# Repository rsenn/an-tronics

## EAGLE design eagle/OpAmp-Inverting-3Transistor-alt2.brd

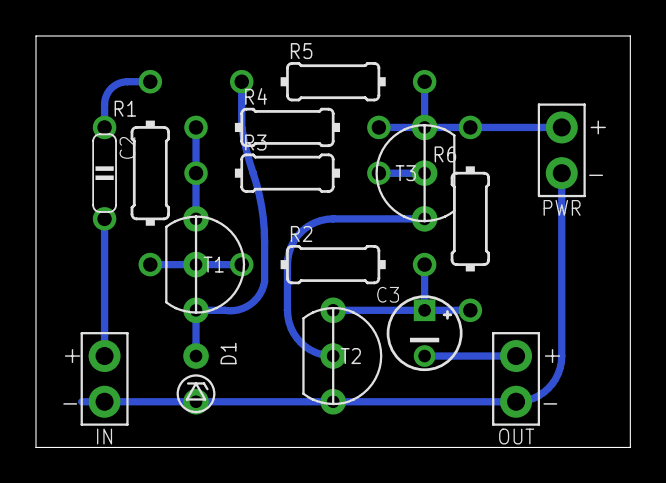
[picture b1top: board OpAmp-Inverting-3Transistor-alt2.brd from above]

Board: 2 copper layers, 33.0 x 22.9 mm, 15 parts (0 on the bottom side), 11 nets.

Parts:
C2: 33nF; C050-020X044
C3: 3.3μF; E2.5-4/V
D1: Z=3.3V; DO34Z2,5
IN: SPAD+--+; SPAD-+
J1: PWR-R
OUT: SPAD+-+-; SPAD+-
R1: 100kΩ; 0204/10-V
R2: 1MΩ; 0204/10
R3: 75kΩ; 0204/10
R4: 7.5kΩ; 0204/10
R5: 4.7kΩ; 0204/10
R6: 1kΩ; 0204/10-V
T1, T2: BC547; TO92-CBE
T3: BC557; TO92-CBE

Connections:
GND: D1.A, IN.1, J1.1, OUT.1, T2.E
unnamed: D1.C, R5.1, T1.E
unnamed: R3.1, R4.1, T1.C
unnamed: T2.B, T3.C
unnamed: C2.2, IN.2
unnamed: C2.1, R1.1
unnamed: R1.2, R2.1, T1.B
unnamed: R3.2, T3.B
unnamed: C3.+, R2.2, R6.2, T2.C
unnamed: C3.-, OUT.2
VCC: J1.2, R4.2, R5.2, R6.1, T3.E

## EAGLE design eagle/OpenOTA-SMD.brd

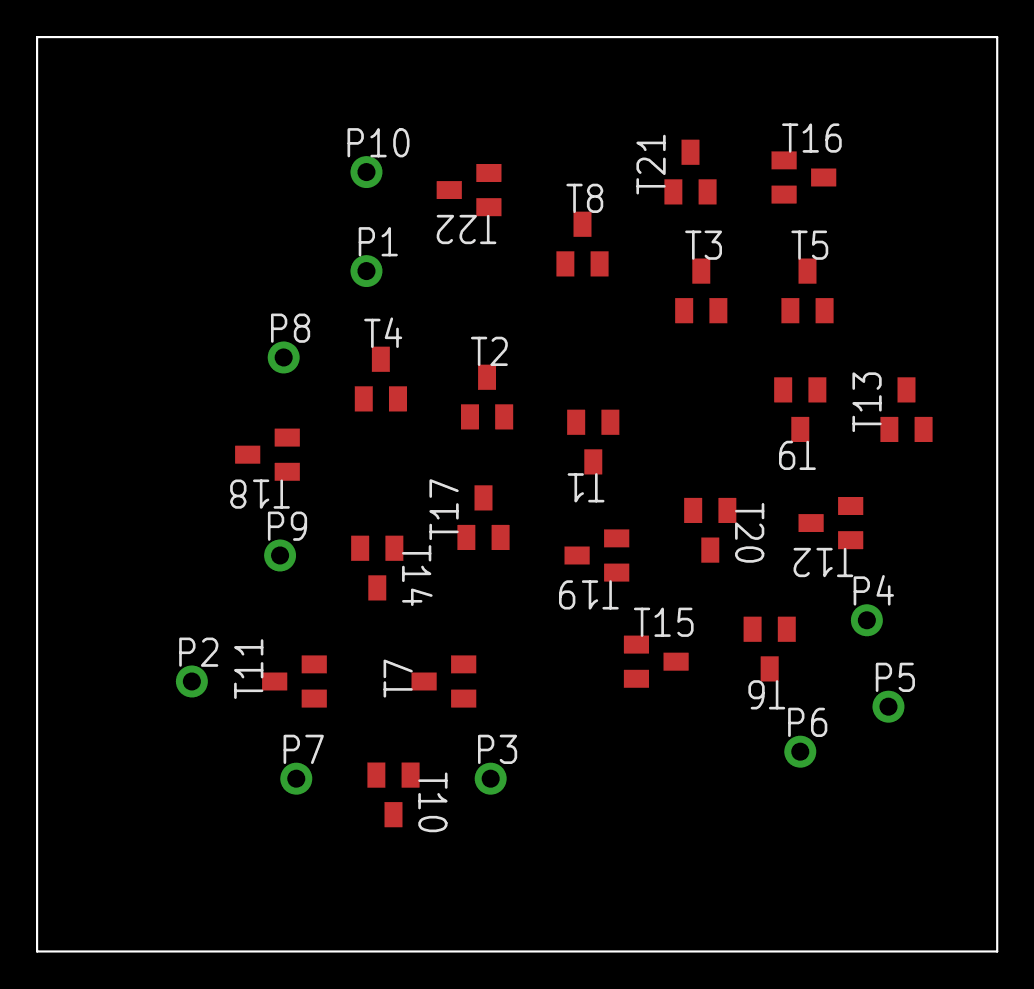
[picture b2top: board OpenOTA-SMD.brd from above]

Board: 2 copper layers, 53.3 x 50.8 mm, 32 parts (0 on the bottom side), 22 nets, no tracks yet.

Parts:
P1, P2, P3, P4, P5, P6, P7, P8, P9, P10: SPAD
T1, T2, T3, T4, T5, T6, T7, T8, T9: BC857; SOT-23
T10, T12, T13, T14, T15, T16, T17, T18, T19, T20, T21, T22: BC847; SOT-23_T10
T11: BC847; SOT-23

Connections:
+15: P1.1, T1.2, T2.2, T3.2, T4.2, T5.2, T6.2
-15: P10.1, T17.2, T18.2, T19.2, T20.2, T21.2, T22.2
IN_A+: P3.1, T10.1
IN_A-: P7.1, T11.1
IN_B+: P5.1, T13.1
IN_B-: P4.1, T12.1
IO_A: P2.1, T7.3, T11.3
I_A: P8.1, T14.1, T17.3
I_B: P9.1, T15.1, T19.3
unnamed: T1.1, T2.1, T2.3, T7.2
unnamed: T1.3, T7.1, T10.3
unnamed: T12.2, T13.2, T15.3
unnamed: T3.1, T4.1, T4.3, T8.2
unnamed: T3.3, T8.1, T12.3
unnamed: T10.2, T11.2, T14.3
unnamed: T8.3, T16.1, T21.3
unnamed: T5.1, T6.1, T6.3, T9.2
unnamed: T5.3, T9.1, T13.3
unnamed: T14.2, T17.1, T18.1, T18.3
unnamed: T15.2, T19.1, T20.1, T20.3
unnamed: T16.2, T21.1, T22.1, T22.3
OB: P6.1, T9.3, T16.3

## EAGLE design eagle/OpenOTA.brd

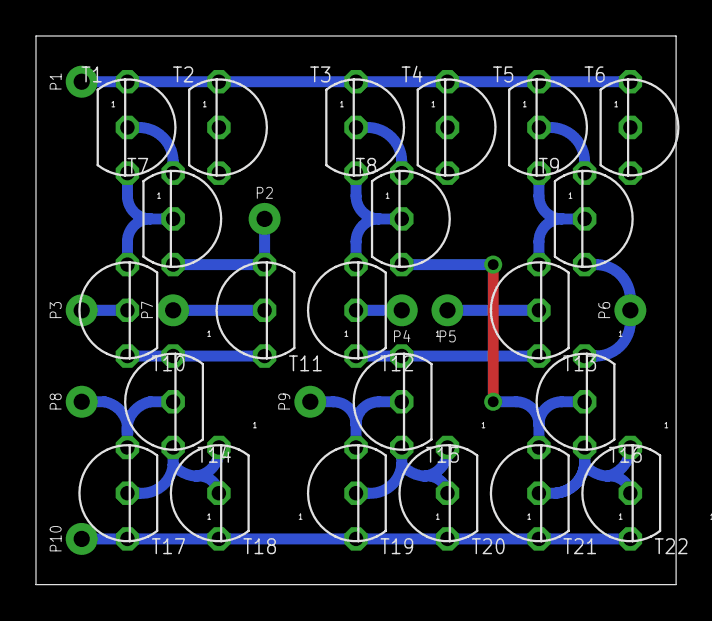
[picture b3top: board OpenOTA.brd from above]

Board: 2 copper layers, 35.6 x 30.5 mm, 32 parts (0 on the bottom side), 22 nets.

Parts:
P1, P2, P3, P4, P5, P6, P7, P8, P9, P10: SPAD
T1, T2, T3, T4, T5, T6, T7, T8, T9: 2N3906; TO92
T10, T11, T12, T13, T14, T15, T16, T17, T18, T19, T20, T21, T22: 2N3904; TO92

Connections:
+15: P1.1, T1.1, T2.1, T3.1, T4.1, T5.1, T6.1
-15: P10.1, T17.1, T18.1, T19.1, T20.1, T21.1, T22.1
IN_A+: P3.1, T10.2
IN_A-: P7.1, T11.2
IN_B+: P5.1, T13.2
IN_B-: P4.1, T12.2
IO_A: P2.1, T7.3, T11.3
I_A: P8.1, T14.2, T17.3
I_B: P9.1, T15.2, T19.3
unnamed: T1.2, T2.2, T2.3, T7.1
unnamed: T1.3, T7.2, T10.3
unnamed: T12.1, T13.1, T15.3
unnamed: T3.2, T4.2, T4.3, T8.1
unnamed: T3.3, T8.2, T12.3
unnamed: T10.1, T11.1, T14.3
unnamed: T8.3, T16.2, T21.3
unnamed: T5.2, T6.2, T6.3, T9.1
unnamed: T5.3, T9.2, T13.3
unnamed: T14.1, T17.2, T18.2, T18.3
unnamed: T15.1, T19.2, T20.2, T20.3
unnamed: T16.1, T21.2, T22.2, T22.3
OB: P6.1, T9.3, T16.3

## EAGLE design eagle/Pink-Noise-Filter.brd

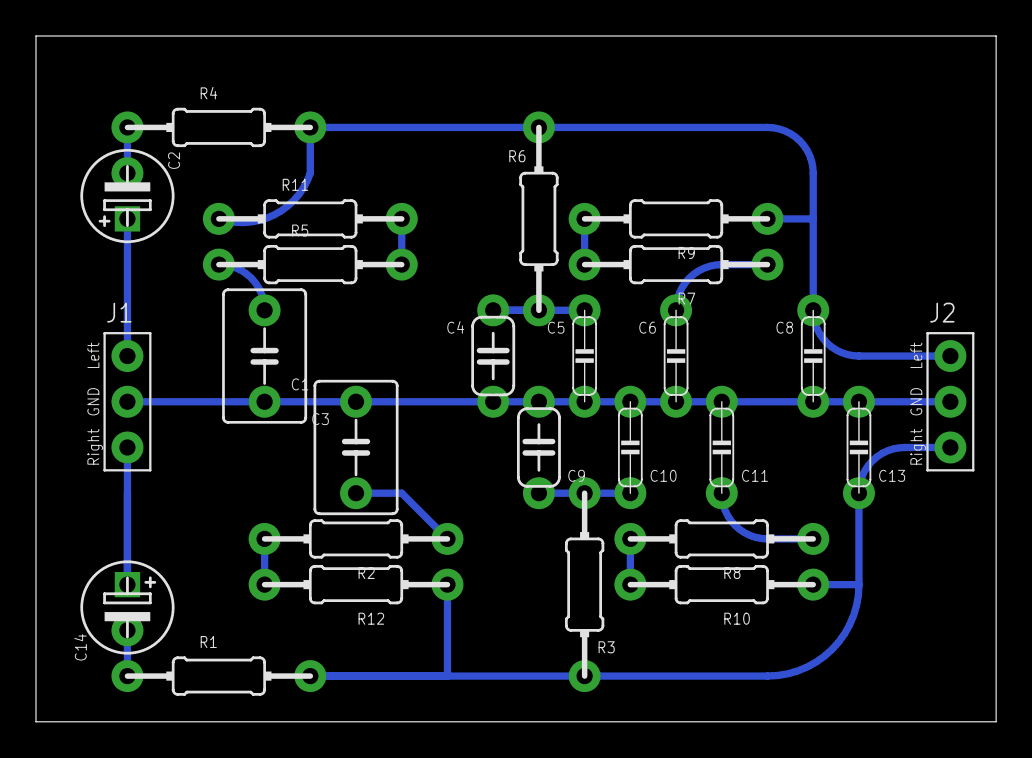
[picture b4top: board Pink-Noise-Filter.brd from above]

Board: 2 copper layers, 53.3 x 38.1 mm, 26 parts (0 on the bottom side), 17 nets.

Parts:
C1, C3: 1µF; C050-045X075/V
C2, C14: 10µF; E2,5-5
C4, C9: 220nF; C050-024X044/V
C5, C10: 47nF; C050-020X044/V
C6, C11: 100nF; C050-020X044/V
C8, C13: 33nF; C050-020X044/V
J1, J2: SAUDIOL-GND-R; SPAD-L-GND-R
R1, R4: 6.8kΩ; 0204/10
R2, R5, R11, R12: 1.5kΩ; 0204/10
R3, R6: 1kΩ; 0204/10-V
R7, R8, R9, R10: 150Ω; 0204/10

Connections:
GND: C1.2, C3.2, C4.2, C5.2, C6.2, C8.2, C9.2, C10.2, C11.2, C13.2, J1.0, J2.0
unnamed: C1.1, R2.1
unnamed: C3.1, R5.1
unnamed: C4.1, C5.1, R6.2
unnamed: C6.1, R7.1
unnamed: C8.1, J2.L, R4.2, R6.1, R9.1, R11.1
unnamed: C2.-, R4.1
unnamed: C9.1, C10.1, R3.2
unnamed: C11.1, R8.1
unnamed: C13.1, J2.R, R1.2, R3.1, R10.1, R12.1
unnamed: C14.-, R1.1
unnamed: C14.+, J1.R
unnamed: C2.+, J1.L
unnamed: R7.2, R9.2
unnamed: R8.2, R10.2
unnamed: R5.2, R11.2
unnamed: R2.2, R12.2

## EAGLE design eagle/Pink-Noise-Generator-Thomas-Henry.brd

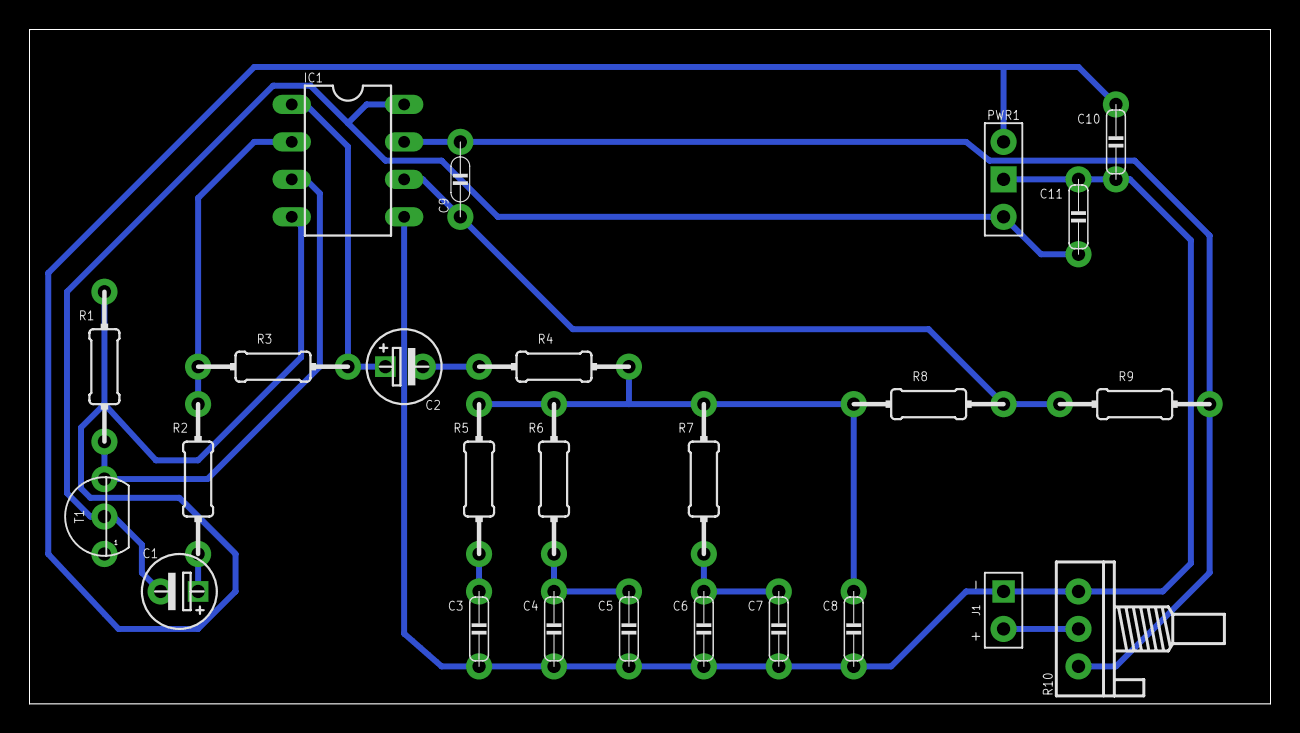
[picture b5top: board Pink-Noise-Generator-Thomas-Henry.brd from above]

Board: 2 copper layers, 84.1 x 45.7 mm, 25 parts (0 on the bottom side), 15 nets.

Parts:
C1, C2: 10µF; E2,5-5
C3: 1µF; C050-020X044/V
C4: 220nF; C050-020X044/V
C5, C6, C7: 47nF; C050-020X044/V
C8: 33nF; C050-020X044/V
C9: 56pF; C050-020X036
C10, C11: 100nF; C050-020X044/V
IC1: TL072P; DIL08
J1: SPAD+-+-; SPAD+-
PWR1: -12V_GND_+12V-VCC-VEE; SPAD-PWR-+GND-
R1: 100kΩ; 0204/10-V
R2: 4.7kΩ; 0204/10-V
R3, R9: 1MΩ; 0204/10
R4: 6.8kΩ; 0204/10
R5: 3kΩ; 0204/10-V
R6: 1kΩ; 0204/10-V
R7: 300Ω; 0204/10-V
R8: 4.7kΩ; 0204/10
R10: 10kΩ; POT
T1: BC547; TO92

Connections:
+12V: C10.1, IC1.4, PWR1.VCC, R1.1
-12V: C1.-, C11.2, IC1.8, PWR1.VEE, T1.2
GND: C3.2, C4.2, C5.2, C6.2, C7.2, C8.2, C10.2, C11.1, IC1.5, J1.1, PWR1.GND, R10.E
unnamed: J1.2, R10.S
unnamed: C3.1, R5.2
unnamed: C4.1, C5.1, R6.2
unnamed: C6.1, C7.1, R7.2
unnamed: C8.1, R4.2, R5.1, R6.1, R7.1, R8.1
unnamed: C2.-, R4.1
unnamed: C2.+, IC1.1, R3.2
unnamed: C1.+, R2.2
unnamed: IC1.2, R2.1, R3.1
unnamed: IC1.3, R1.2, T1.3
unnamed: C9.1, IC1.6, R8.2, R9.1
unnamed: C9.2, IC1.7, R9.2, R10.A

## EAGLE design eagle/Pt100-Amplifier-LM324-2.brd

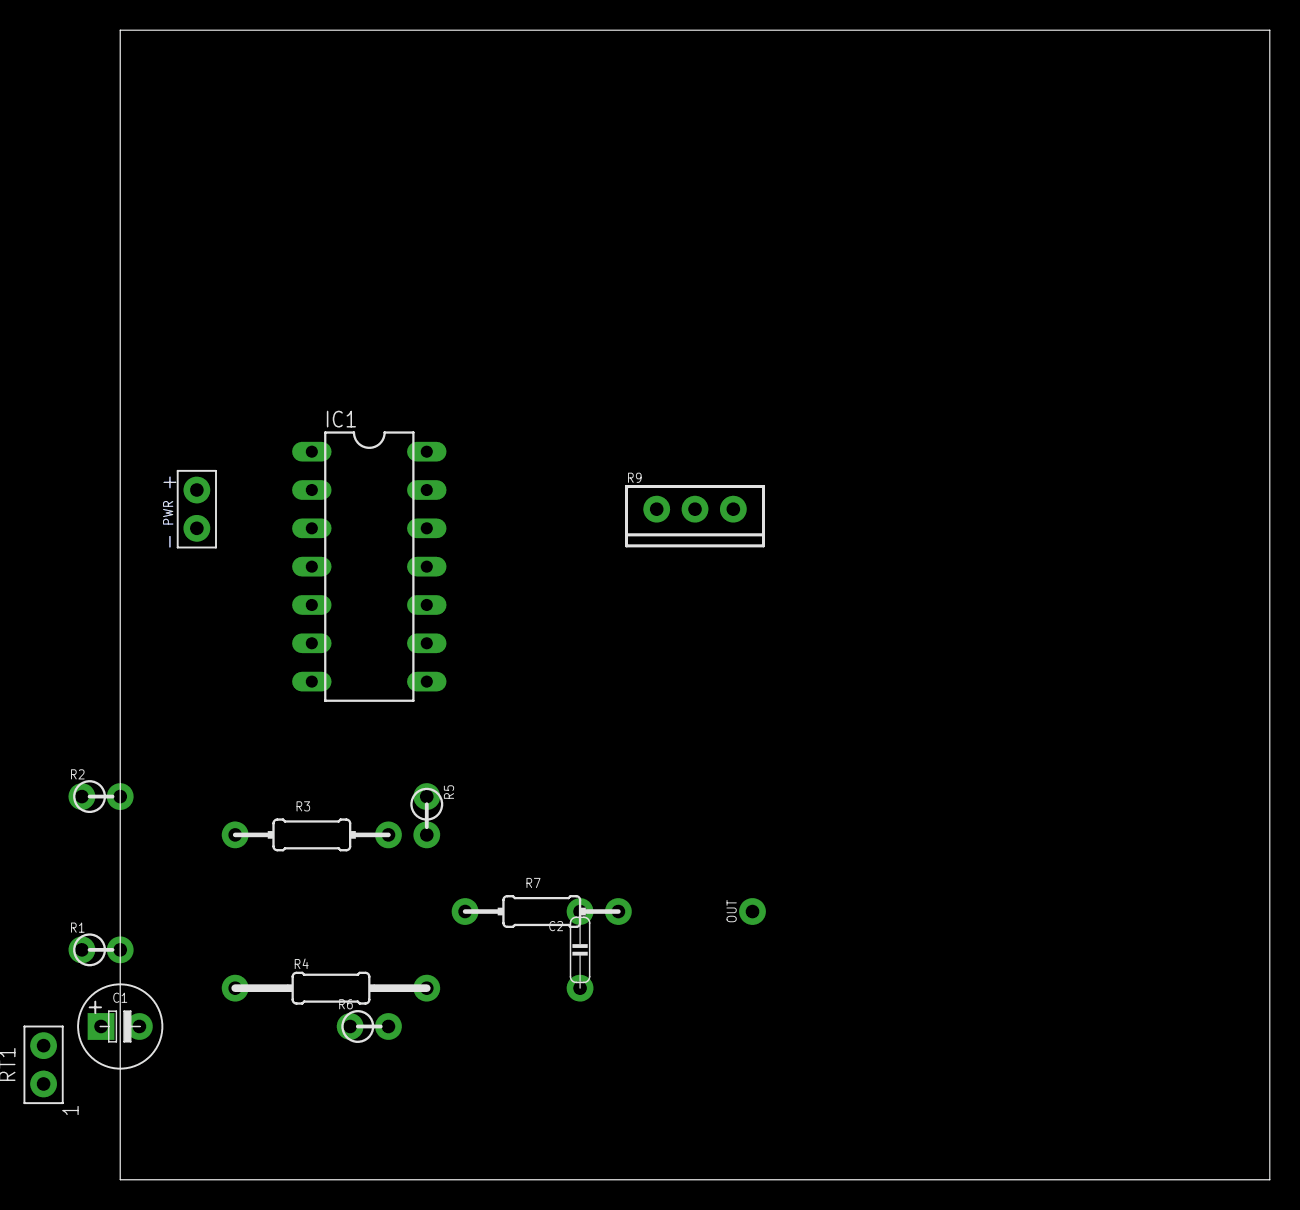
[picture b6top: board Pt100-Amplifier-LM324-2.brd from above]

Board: 2 copper layers, 76.2 x 76.2 mm, 14 parts (0 on the bottom side), 10 nets, no tracks yet.

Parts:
C1: 100uF; E2,5-6
C2: 100nF; C050-020X044/V
IC1: LM324N; DIL14
OUT: HPORT; SPAD
R1: 1k; 0204/2.54
R2, R5, R6: 47k; 0204/2.54
R3: 10k; 0204/10
R4: 10k; 0204/12
R7: 220k; 0204/10
R9: TRIM-POT
RT1: SPAD-2
S5: VCC_GNDPWR-L; PWR-L

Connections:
GND: C1.-, C2.2, IC1.11, R6.2, R9.E, RT1.2, S5.1
unnamed: C1.+, IC1.3, R1.2, RT1.1
unnamed: IC1.1, IC1.2, R4.1
unnamed: IC1.10, R4.2, R6.1
unnamed: IC1.9, R3.2, R5.1
unnamed: IC1.8, R5.2, R7.1
unnamed: C2.1, OUT.1, R7.2
unnamed: IC1.6, IC1.7, R3.1
unnamed: IC1.5, R2.2, R9.A, R9.S
VCC: IC1.4, R1.1, R2.1, S5.2
